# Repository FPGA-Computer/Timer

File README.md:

STM8S003 Timer

This is a timer for watering plant and supplyment light in the winter with LED.
There is a simple menu system (UI.C,UI.H) for setting preferences that may be of interest.

Schematic/layout: Eagle CAD. Firmware compiled using "Free" Cosmic C for the STM8 series.

Project page:

https://hw-by-design.blogspot.com/2018/10/stm8-timer.html

Licensing:

Firmware: Unless otherwise stated are in GPL3.0. stm8s.h is licensed under "MCD-ST Liberty SW License Agreement V2"

Schematic: Creative Commons 4.0 Attribution 4.0 International

PCB & Layout: Creative Commons 4.0 Attribution 4.0 International

See https://creativecommons.org/licenses/by/4.0/

Change log
- back port from LED clock project: NCO for better trimming, Daylight Saving Time, Date and leap year

- Mar 18 2020: Servo support + fixing alarm remainder time after time adjustment

- Mar 4 2021: V2 hardware/firmware release.  V1 will no longer be maintained

Hardware changes:

* Supercap backup power, switcher module

* Different connector for LED/sensor + Servo connector

* LCD, buttons I/O changes. LCD backlight on/off control by ambient light

* I2C connector

* expansion connector for nRF24 (no firmware support)

See https://hw-by-design.blogspot.com/2020/03/stm8-timer-servo-controlled-water-valve.html

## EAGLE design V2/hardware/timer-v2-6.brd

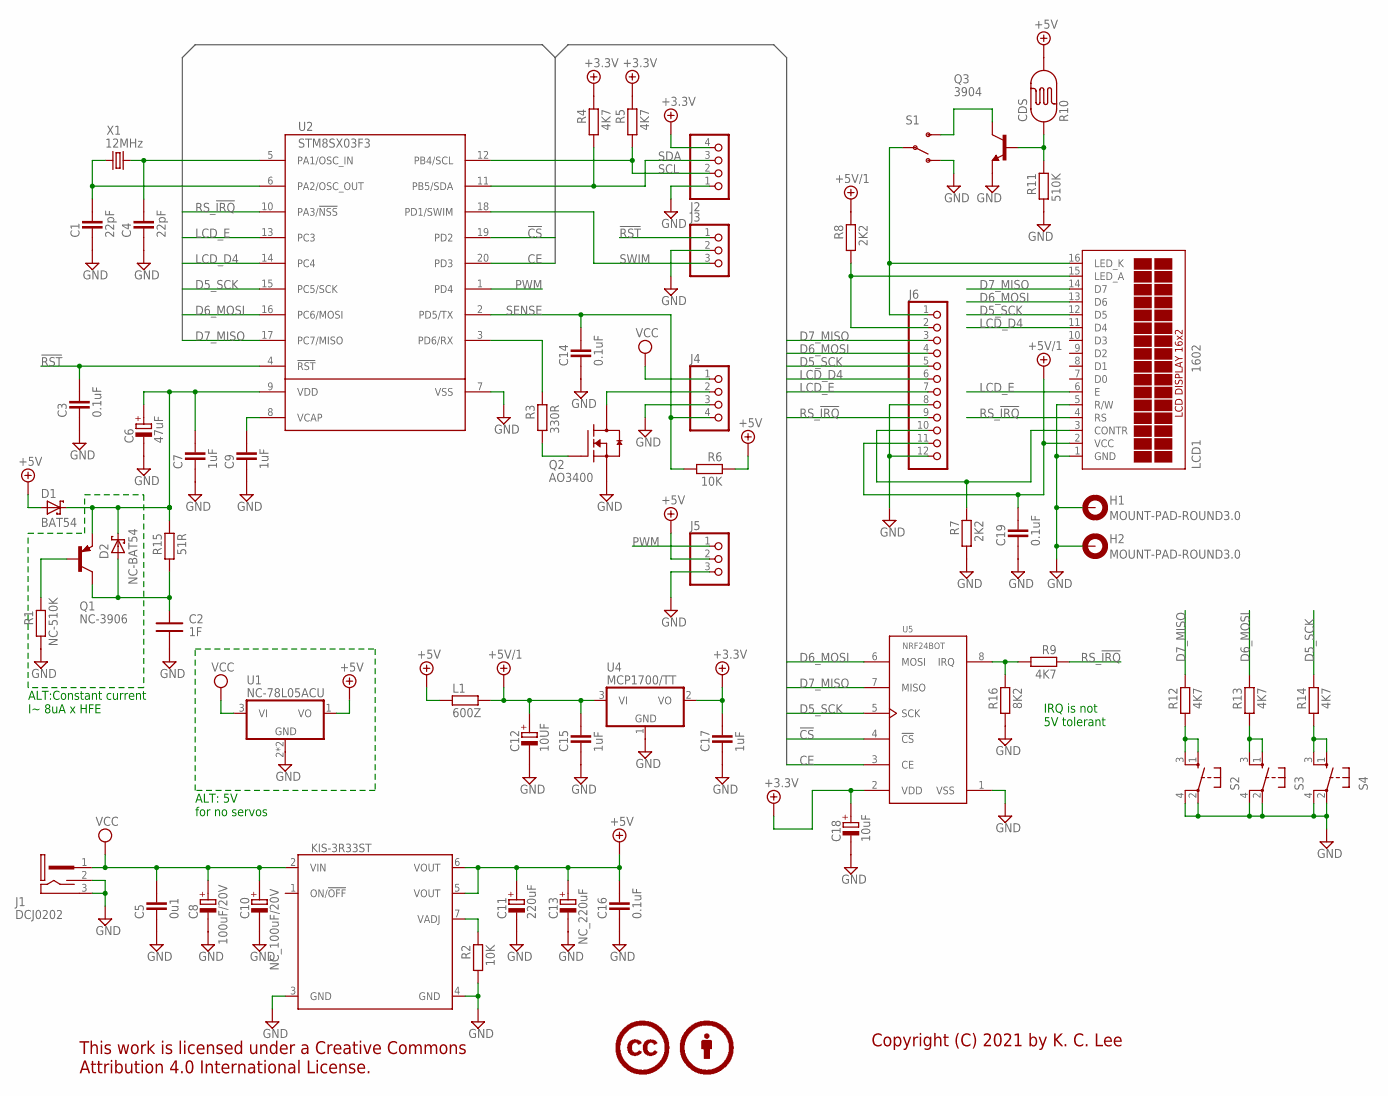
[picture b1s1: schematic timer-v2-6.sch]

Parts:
C1, C4: 22pF; CAPC1608X92N
C2: 1F; ELNA_DB_LOW
C3, C14, C19: 0.1uF; CAPC1608X92N
C5: 0u1; CAPC3215X168N
C6: 47uF; CAPMP7343X310N
C7, C9, C15, C17: 1uF; CAPC1608X92N
C8: 100uF/20V; CAPMP7343X430N
C10: NC_100uF/20V; CAPMP7343X430N
C11: 220uF; CAPMP7343X430N
C12: 10UF; CAPMP6032X280N
C13: NC_220uF; CAPMP7343X430N
C16: 0.1uF; CAPC3215X168N
C18: 10uF; CAPMP6032X280N
D1: BAT54; SOT95P280X135-3N
D2: NC-BAT54; SOT95P280X135-3N
H1, H2: MOUNT-PAD-ROUND3.0; 3,0-PAD
J1: DCJ0202; DCJ0202-SLOTTED
J2: PINHD-1X4_2.54-90°; 1X04/90
J3, J5: PINHD-1X3_2.54; 1X03
J4: PINHD-1X4_2.54; 1X04
J6: PINHD-1X12_2.54; 1X12
L1: 600Z; RESC2012X70N
LCD1: 1602; TUXGR_16X2_R2_NM
LICENSE1: CC-BY100%; CC-BY-100
Q1: NC-3906; SOT95P280X135-3N
Q2: AO3400; SOT95P280X135-3N
Q3: 3904; SOT95P280X135-3N
R1: NC-510K; RESC1608X55N
R2, R6: 10K; RESC1608X55N
R3: 330R; RESC1608X55N
R4, R5, R9, R12, R13, R14: 4K7; RESC1608X55N
R7, R8: 2K2; RESC1608X55N
R10: CDS; PHOTOCELL
R11: 510K; RESC1608X55N
R15: 51R; RESC1608X55N
R16: 8K2; RESC1608X55N
S1: SWITCH-SPDTPTH; SWITCH-SPDT
S2, S3, S4: MOM_SWTH; MOM_SW
U1: NC-78L05ACU; SOT89
U2: STM8SX03F3; TSSOP20
U3: KIS-3R33ST; KIS-3R33S-THRU
U4: MCP1700/TT; SOT95P280X135-3N
U5: NRF24BOT; NRF24L01-BOT
X1: 12MHz; HC49U-V

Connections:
!CS: U2.19 (PD2), U5.4 (!CS)
!RST: C3.2, J3.1, U2.4 (!RST)
+3.3V: C17.2, C18.+, J2.4, R4.1, R5.1, U4.2 (VO), U5.2 (VDD)
+5V: C11.+, C13.+, C16.2, D1.1 (A), J5.2, L1.1, R6.1, R10.2, U1.1 (VO), U3.5 (VOUT), U3.6 (VOUT)
+5V/1: C12.+, C15.2, C19.2, J6.11, L1.2, LCD1.2 (VCC), R8.1, U4.3 (VI)
CE: U2.20 (PD3), U5.3 (CE)
D5_SCK: J6.5, LCD1.12 (D5), R14.1, U2.15 (PC5/SCK), U5.5 (SCK)
D6_MOSI: J6.4, LCD1.13 (D6), R13.1, U2.16 (PC6/MOSI), U5.6 (MOSI)
D7_MISO: J6.3, LCD1.14 (D7), R12.1, U2.17 (PC7/MISO), U5.7 (MISO)
GND: C1.1, C2.-, C3.1, C4.1, C5.1, C6.-, C7.1, C8.-, C9.1, C10.-, C11.-, C12.-, C13.-, C14.1, C15.1, C16.1, C17.1, C18.-, C19.1, H1.B3,0, H2.B3,0, J1.2, J1.3, J2.1, J3.2, J4.3, J5.3, J6.8, J6.12, LCD1.1 (GND), LCD1.5 (R/W), Q2.2 (S), Q3.2 (E), R1.2, R2.2, R7.2, R11.2, R16.2, S1.1 (O), S2.2 (3), S2.4, S3.2 (3), S3.4, S4.2 (3), S4.4, U1.2 (GND), U1.4 (GND), U2.7 (VSS), U3.3 (GND), U3.4 (GND), U4.1 (GND), U5.1 (VSS)
LCD_A: J6.2, LCD1.15 (LED_A), R8.2
LCD_D4: J6.6, LCD1.11 (D4), U2.14 (PC4)
LCD_E: J6.7, LCD1.6 (E), U2.13 (PC3)
unnamed: J4.2, Q2.3 (D)
unnamed: C9.2, U2.8 (VCAP)
unnamed: R2.1, U3.7 (VADJ)
unnamed: C4.2, U2.5 (PA1/OSC_IN), X1.2
unnamed: C1.2, U2.6 (PA2/OSC_OUT), X1.1
unnamed: J6.1, LCD1.16 (LED_K), S1.2
unnamed: C6.+, C7.2, D1.3 (K), D2.3 (K), Q1.2 (E), R15.1, U2.9 (VDD)
unnamed: C2.+, D2.1 (A), Q1.3 (C), R15.2
unnamed: R14.2, S4.1, S4.3 (2)
unnamed: Q1.1 (B), R1.1
unnamed: Q3.1 (B), R10.1, R11.1
unnamed: Q2.1 (G), R3.2
unnamed: R3.1, U2.3 (PD6/RX)
unnamed: R13.2, S3.1, S3.3 (2)
unnamed: R12.2, S2.1, S2.3 (2)
unnamed: R9.2, R16.1, U5.8 (IRQ)
unnamed: Q3.3 (C), S1.3 (S)
unnamed: J6.10, LCD1.3 (CONTR), R7.1
PWM: J5.1, U2.1 (PD4)
RS_!IRQ: J6.9, LCD1.4 (RS), R9.1, U2.10 (PA3/!NSS)
SCL: J2.2, R5.2, U2.12 (PB4/SCL)
SDA: J2.3, R4.2, U2.11 (PB5/SDA)
SENSE: C14.2, J4.4, R6.2, U2.2 (PD5/TX)
SWIM: J3.3, U2.18 (PD1/SWIM)
VCC: C5.2, C8.+, C10.+, J1.1, J4.1, U1.3 (VI), U3.2 (VIN)

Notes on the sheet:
Copyright (C) 2021 by K. C. Lee
ALT: 5V for no servos
ALT:Constant current I~ 8uA x HFE
IRQ is not 5V tolerant

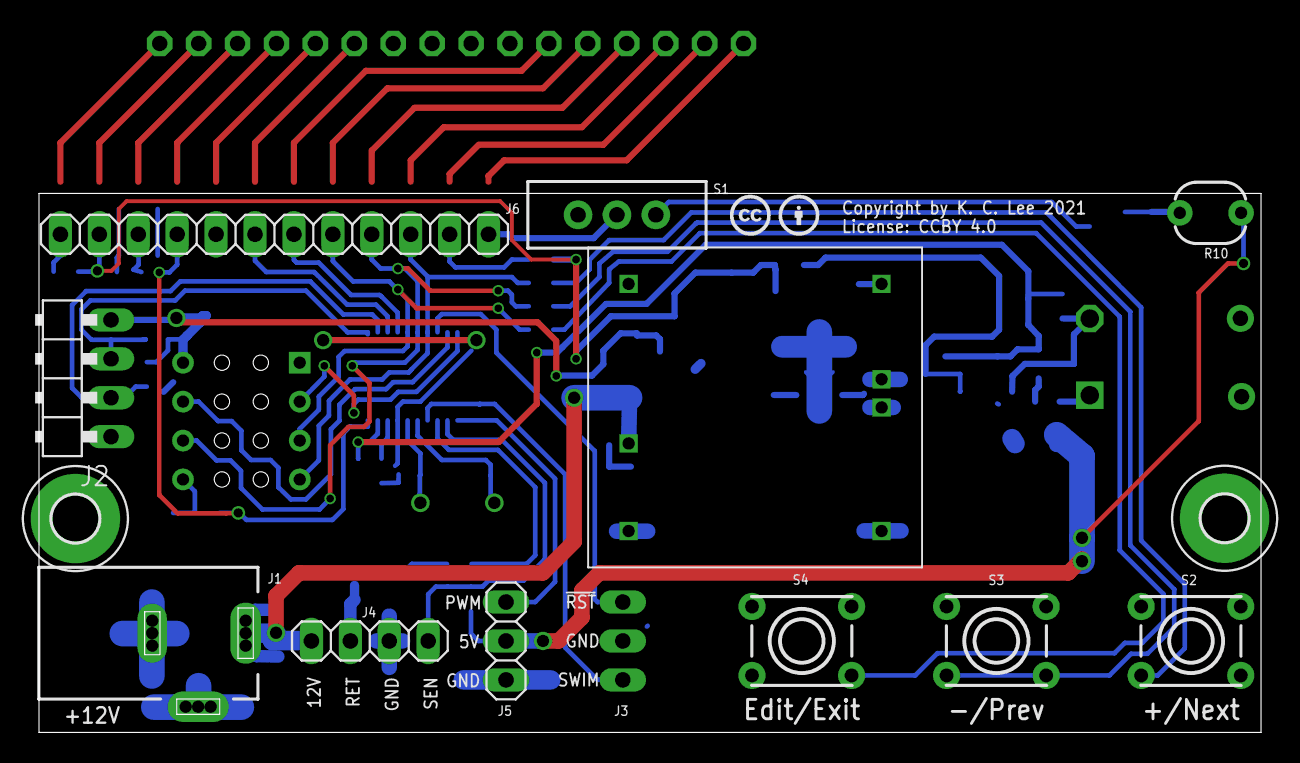
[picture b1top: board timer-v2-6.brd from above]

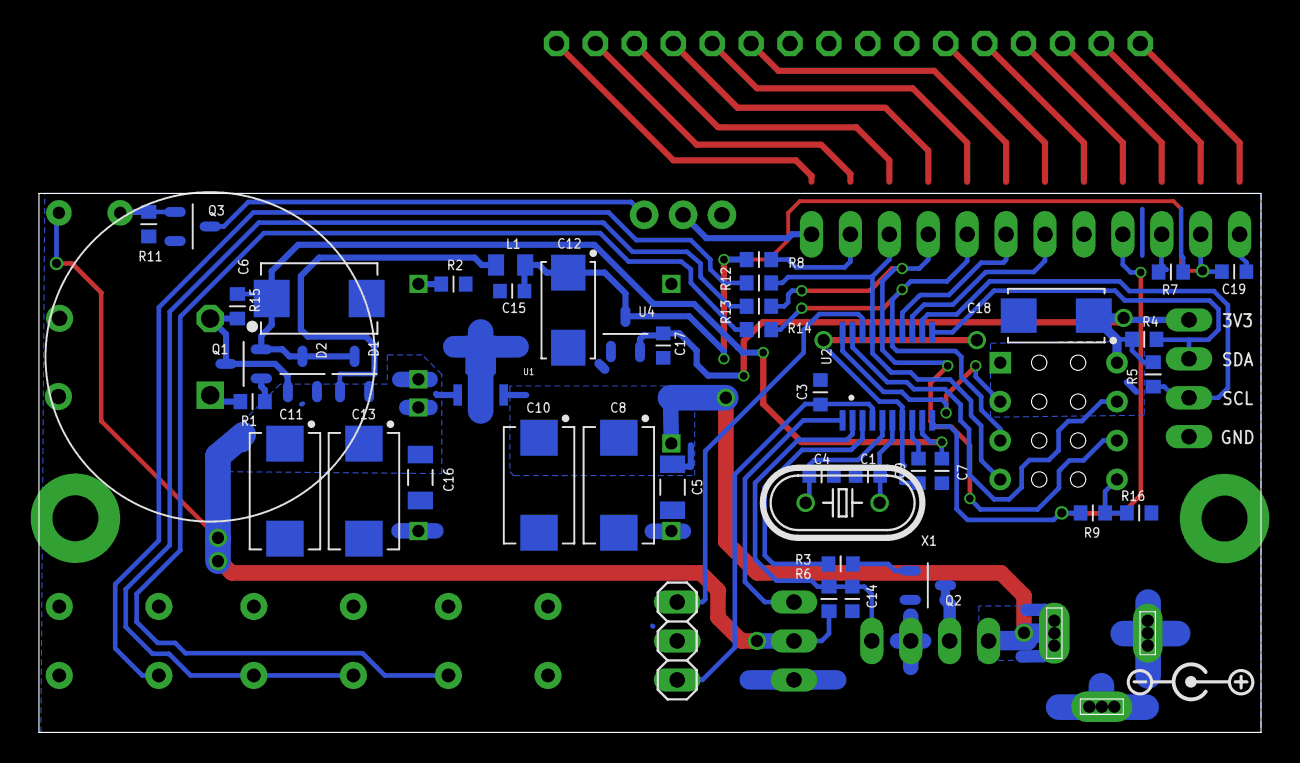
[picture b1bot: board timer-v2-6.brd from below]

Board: 2 copper layers, 79.8 x 35.2 mm, 62 parts (47 on the bottom side), 38 nets.

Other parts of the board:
U$1: POLARITY

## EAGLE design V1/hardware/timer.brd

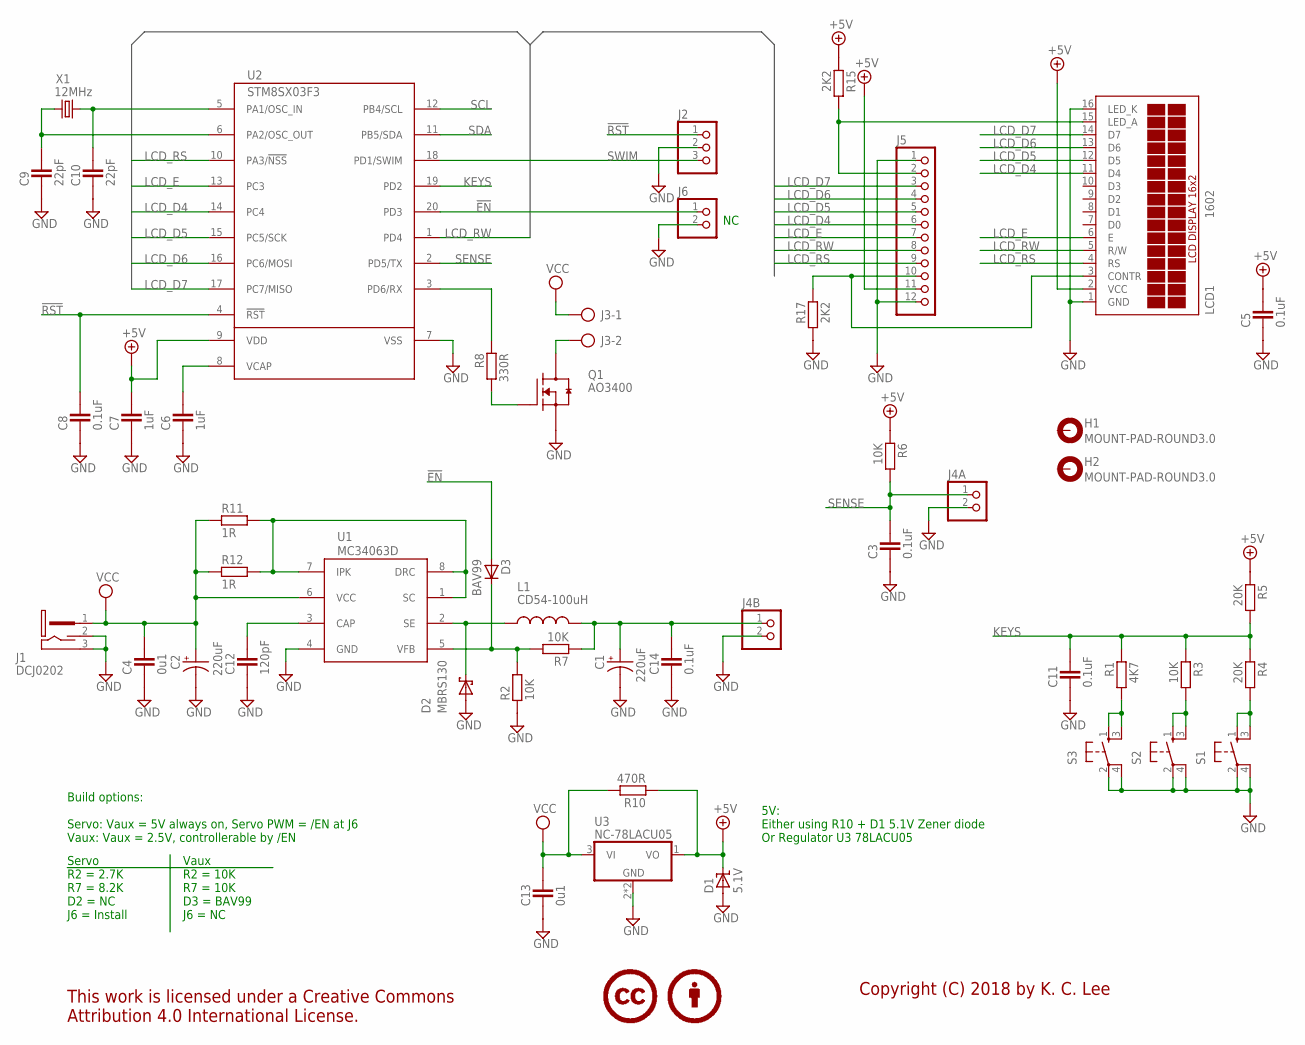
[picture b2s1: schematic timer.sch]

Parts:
C1, C2: 220uF; PANASONIC_G
C3, C5, C8, C11: 0.1uF; CAPC1608X92N
C4, C13: 0u1; CAPC2012X145AN
C6, C7: 1uF; CAPC1608X92N
C9, C10: 22pF; CAPC1608X92N
C12: 120pF; CAPC3215X168N
C14: 0.1uF; CAPC2012X145AN
D1: 5.1V; SOD2514X100N
D2: MBRS130; DIOM5436X265N
D3: BAV99; SOT95P280X135-3N
H1, H2: MOUNT-PAD-ROUND3.0; 3,0-PAD
J1: DCJ0202; DCJ0202-SLOTTED
J2: PINHD-1X3_2.54; 1X03
J3: AK500/2
J4A, J4B, J6: PINHD-1X2_2.54; 1X02
J5: PINHD-1X12_2.54; 1X12
L1: CD54-100uH; CD54
LCD1: 1602; TUXGR_16X2_R2_NM
LICENSE1: CC-BY100%; CC-BY-100
Q1: AO3400; SOT95P280X135-3N
R1: 4K7; RESC1608X55N
R2, R3, R6, R7: 10K; RESC1608X55N
R4, R5: 20K; RESC1608X55N
R8: 330R; RESC1608X55N
R10: 470R; RESC1608X55N
R11, R12: 1R; RESC2012X70N
R15, R17: 2K2; RESC1608X55N
S1, S2, S3: MOM_SWTH; MOM_SW
U1: MC34063D; SO-8
U2: STM8SX03F3; TSSOP20
U3: NC-78LACU05; SOT89
X1: 12MHz; SM49

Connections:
!EN: D3.1 (A), J6.1, U2.20 (PD3)
!RST: C8.2, J2.1, U2.4 (!RST)
+5V: C5.2, C7.2, D1.K, J5.11, LCD1.2 (VCC), R5.1, R6.1, R10.1, R15.1, U2.9 (VDD), U3.1 (VO)
+VOUT: C1.+, C14.2, J4B.1, L1.2, R7.1
GND: C1.-, C2.-, C3.1, C4.1, C5.1, C6.1, C7.1, C8.1, C9.1, C10.1, C11.1, C12.1, C13.1, C14.1, D1.A, D2.A, J1.2, J1.3, J2.2, J4A.2, J4B.2, J5.1, J5.12, J6.2, LCD1.1 (GND), LCD1.16 (LED_K), Q1.2 (S), R2.1, R17.2, S1.2 (3), S1.4, S2.2 (3), S2.4, S3.2 (3), S3.4, U1.4 (GND), U2.7 (VSS), U3.2 (GND), U3.4 (GND)
KEYS: C11.2, R1.1, R3.1, R4.1, R5.2, U2.19 (PD2)
LCD_A: J5.2, LCD1.15 (LED_A), R15.2
LCD_D4: J5.6, LCD1.11 (D4), U2.14 (PC4)
LCD_D5: J5.5, LCD1.12 (D5), U2.15 (PC5/SCK)
LCD_D6: J5.4, LCD1.13 (D6), U2.16 (PC6/MOSI)
LCD_D7: J5.3, LCD1.14 (D7), U2.17 (PC7/MISO)
LCD_E: J5.7, LCD1.6 (E), U2.13 (PC3)
LCD_RS: J5.9, LCD1.4 (RS), U2.10 (PA3/!NSS)
LCD_RW: J5.8, LCD1.5 (R/W), U2.1 (PD4)
unnamed: J3.2, Q1.3 (D)
unnamed: C6.2, U2.8 (VCAP)
unnamed: D3.3 (K), R2.2, R7.2, U1.5 (VFB)
unnamed: C10.2, U2.5 (PA1/OSC_IN), X1.2
unnamed: C9.2, U2.6 (PA2/OSC_OUT), X1.1
unnamed: R11.2, R12.2, U1.1 (SC), U1.7 (IPK), U1.8 (DRC)
unnamed: D2.K, L1.1, U1.2 (SE)
unnamed: C12.2, U1.3 (CAP)
unnamed: R4.2, S1.1, S1.3 (2)
unnamed: Q1.1 (G), R8.2
unnamed: R8.1, U2.3 (PD6/RX)
unnamed: R3.2, S2.1, S2.3 (2)
unnamed: R1.2, S3.1, S3.3 (2)
unnamed: J5.10, LCD1.3 (CONTR), R17.1
SCL: U2.12 (PB4/SCL)
SDA: U2.11 (PB5/SDA)
SENSE: C3.2, J4A.1, R6.2, U2.2 (PD5/TX)
SWIM: J2.3, U2.18 (PD1/SWIM)
VCC: C2.+, C4.2, C13.2, J1.1, J3.1, R10.2, R11.1, R12.1, U1.6 (VCC), U3.3 (VI)

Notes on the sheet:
Copyright (C) 2018 by K. C. Lee
Servo R2 = 2.7K R7 = 8.2K D2 = NC J6 = Install
Vaux R2 = 10K R7 = 10K D3 = BAV99 J6 = NC
Build options: Servo: Vaux = 5V always on, Servo PWM = /EN at J6 Vaux: Vaux = 2.5V, controllerable by /EN
5V: Either using R10 + D1 5.1V Zener diode Or Regulator U3 78LACU05

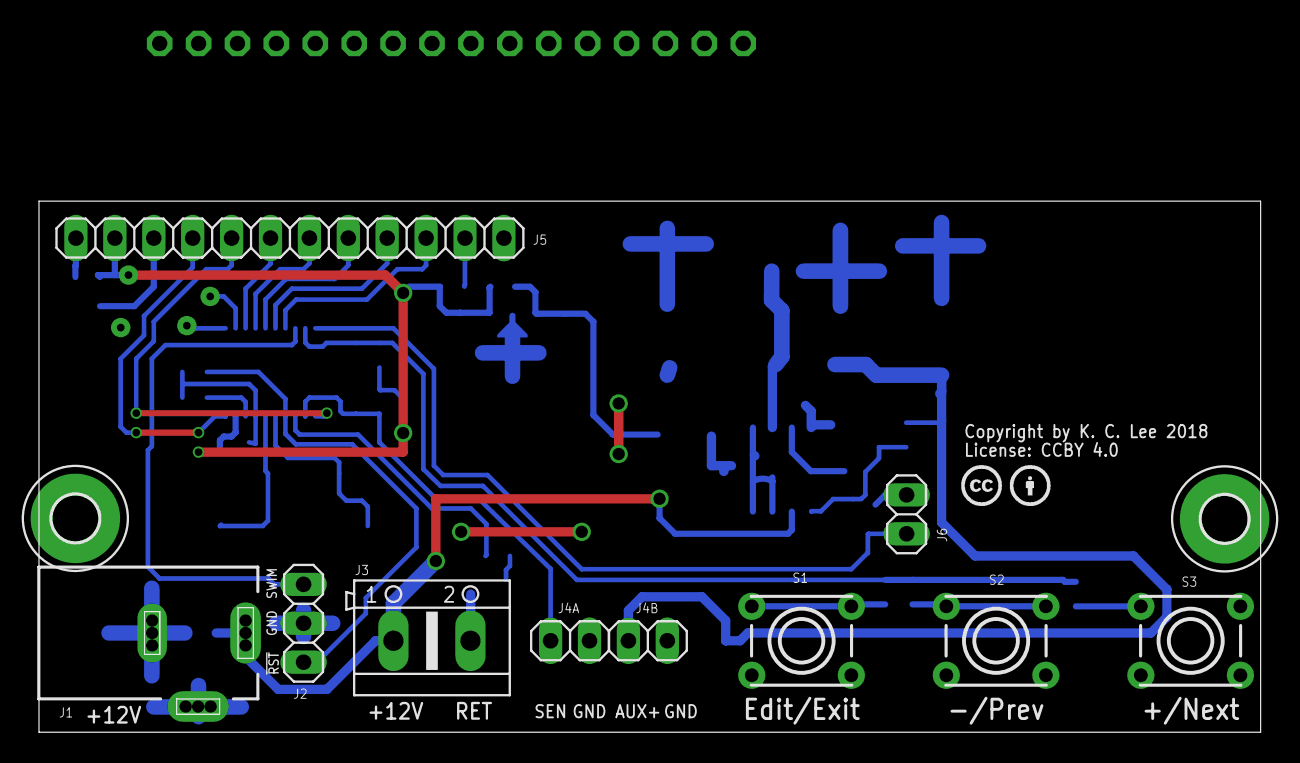
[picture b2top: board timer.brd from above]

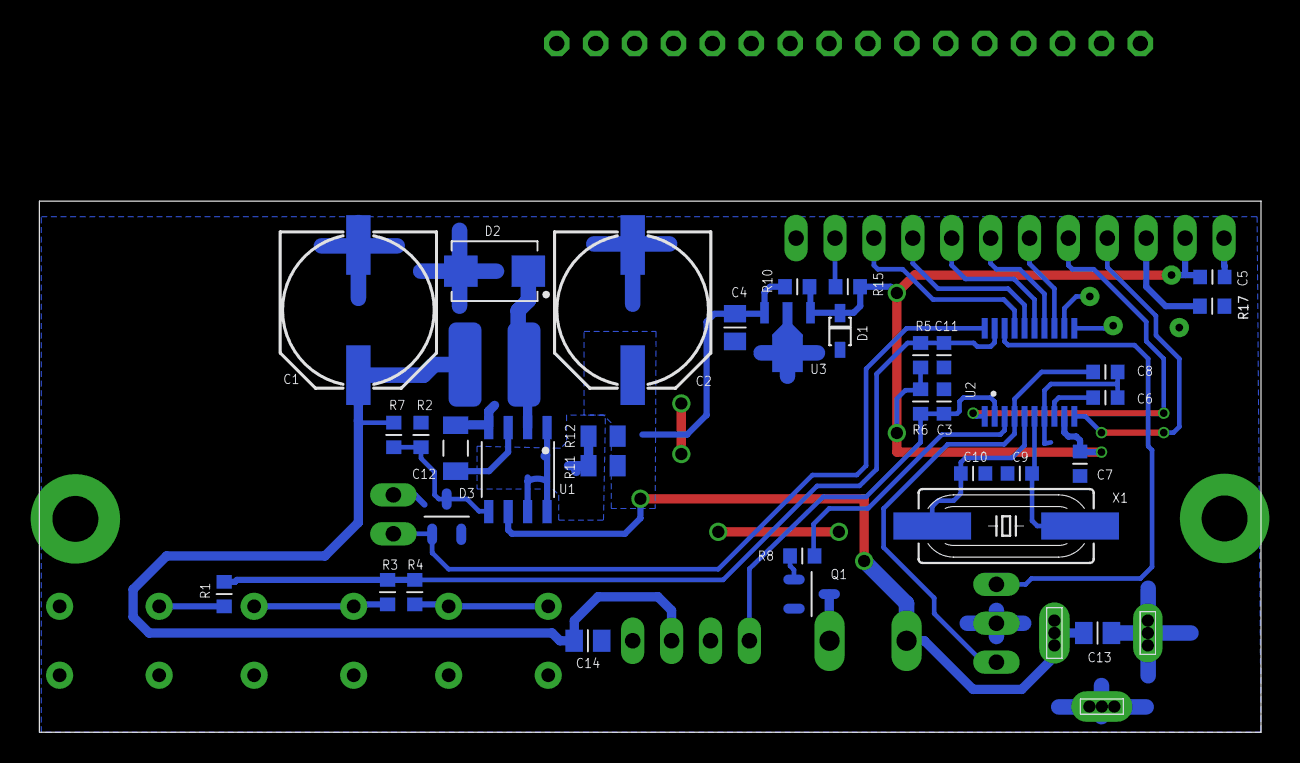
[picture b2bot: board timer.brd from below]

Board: 2 copper layers, 79.8 x 34.7 mm, 50 parts (36 on the bottom side), 31 nets.

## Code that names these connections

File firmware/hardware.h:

/*
 * hardware.h
 *
 * Created: October-19-18, 12:25:42 PM
 *  Author: K. C. Lee
 * Copyright (c) 2016 by K. C. Lee
 
 This program is free software: you can redistribute it and/or modify
 it under the terms of the GNU General Public License as published by
 the Free Software Foundation, either version 3 of the License, or
 (at your option) any later version.

 This program is distributed in the hope that it will be useful,
 but WITHOUT ANY WARRANTY; without even the implied warranty of
 MERCHANTABILITY or FITNESS FOR A PARTICULAR PURPOSE.  See the
 GNU General Public License for more details.

 You should have received a copy of the GNU General Public License
 along with this program.

 If not, see http://www.gnu.org/licenses/gpl-3.0.en.html 
 */ 

#ifndef HARDWARE_H_
#define HARDWARE_H_

#ifndef __CSMC__
#define __CSMC__
#endif
#define STM8S003

#include "stm8s.h"
#include <stdio.h>

#define AUX_SERVO								// comment line for VAux control

// STM8S003F3P6
enum _PA { PA1=0x02, PA2=0x04, PA3=0x08 };
enum _PB { PB4=0x10, PB5=0x20 };
enum _PC { PC3=0x08, PC4=0x10, PC5=0x20, PC6=0x40, PC7=0x80 };
enum _PD { PD1=0x02, PD2=0x04, PD3=0x08, PD4=0x10, PD5=0x20, PD6=0x40 };

#include "irq.h"

#define CPU_CLOCK								12000000UL
#define EE_Addr									0x4000

#define LCD_E										PC3
#define LCD_RW									PD4
#define LCD_DATA								(PC4|PC5|PC6|PC7)
#define LCD_RS									PA3

#define LCD_RW_PORT							GPIOD
#define LCD_RS_PORT							GPIOA
#define LCD_E_PORT							GPIOC
#define LCD_DATA_PORT						GPIOC

#define MOTOR_EN								PD3
#define LED_EN									PD6
#define PERIPH_PORT							GPIOD

#define LED_OFF()								PERIPH_PORT->ODR &= ~LED_EN
#define LED_ON()								PERIPH_PORT->ODR |= LED_EN

#define ADC_KEYS								3
#define ADC_SENSE								5

#define ADC_MAX									1023
#define ADC_HYSTERESIS					5

#define DATA_KEY1								0xAE
#define DATA_KEY2								0x56

#ifdef AUX_SERVO									// Aux control servo

	#define SERVO_FREQ							50
	#define TIM2_DIV								4
	#define TIM2_PSC								2			// 2^2
	#define TIM2_RELOAD							(CPU_CLOCK/(TIM2_DIV*SERVO_FREQ))

// 12MHz/4 = 3MHz, resolution: 333ns
// Servo : 1.5ms + 0.5ms* X/90 
// Actual position determined empirically

	#define SERVO_OFF								4600
	#define SERVO_ON								1400

// wait 8 sec before shut down
	#define SERVO_SHUTDOWN					(SERVO_FREQ*10)

	extern uint8_t 	ServoFlag;
	void Servo_Init(void);
	void Servo_State(uint8_t State);

	#define MOTOR_OFF()							Servo_State(0)
	#define MOTOR_ON()							Servo_State(1)
	#define MOTOR_FLAG							ServoFlag
	
#else															// Aux control AUX regulator

	#define MOTOR_OFF()							PERIPH_PORT->ODR |= MOTOR_EN
	#define MOTOR_ON()							PERIPH_PORT->ODR &= ~MOTOR_EN
	#define MOTOR_FLAG							!(PERIPH_PORT->ODR & MOTOR_EN)
#endif

#include "LCD.h"
#include "time.h"
#include "adc.h"
#include "key.h"
#include "ui.h"
#include "eeprom.h"
#include "menu.h"

void Init_Hardware(void);
void Delay(uint16_t Delay);


#endif

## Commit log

2018-11-01 re-release - update+fix licensing
2018-11-01 Changes to reload value
2018-11-02 small oopies
2018-11-20 GUI enhancements
2018-11-21 Fix clock trim polarity
2020-01-20 NCO,DST,Date,Leap year
2020-01-26 Bug fix: Day of week, key repeat rate
2020-02-05 Set DST states after time/date set
2020-03-18 Servo support + alarm remainder time
2020-11-01 fix daylight saving time
2020-12-03 bug fix
2021-03-04 add V2 hardware+firmware
2021-03-09 fix DST start/end dates

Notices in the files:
V1/hardware/timer.brd:
Copyright by K. C. Lee 2018
License: CCBY 4.0
V2/hardware/timer-v2-6.brd:
Copyright by K. C. Lee 2021
parts and their libraries:
Misc logo: This work is licensed under a Creative Commons
Attribution 4.0 International License.
SparkFun-Sensors: Licensing: Creative Commons ShareAlike 4.0 International - https://creativecommons.org/licenses/by-sa/4.0
